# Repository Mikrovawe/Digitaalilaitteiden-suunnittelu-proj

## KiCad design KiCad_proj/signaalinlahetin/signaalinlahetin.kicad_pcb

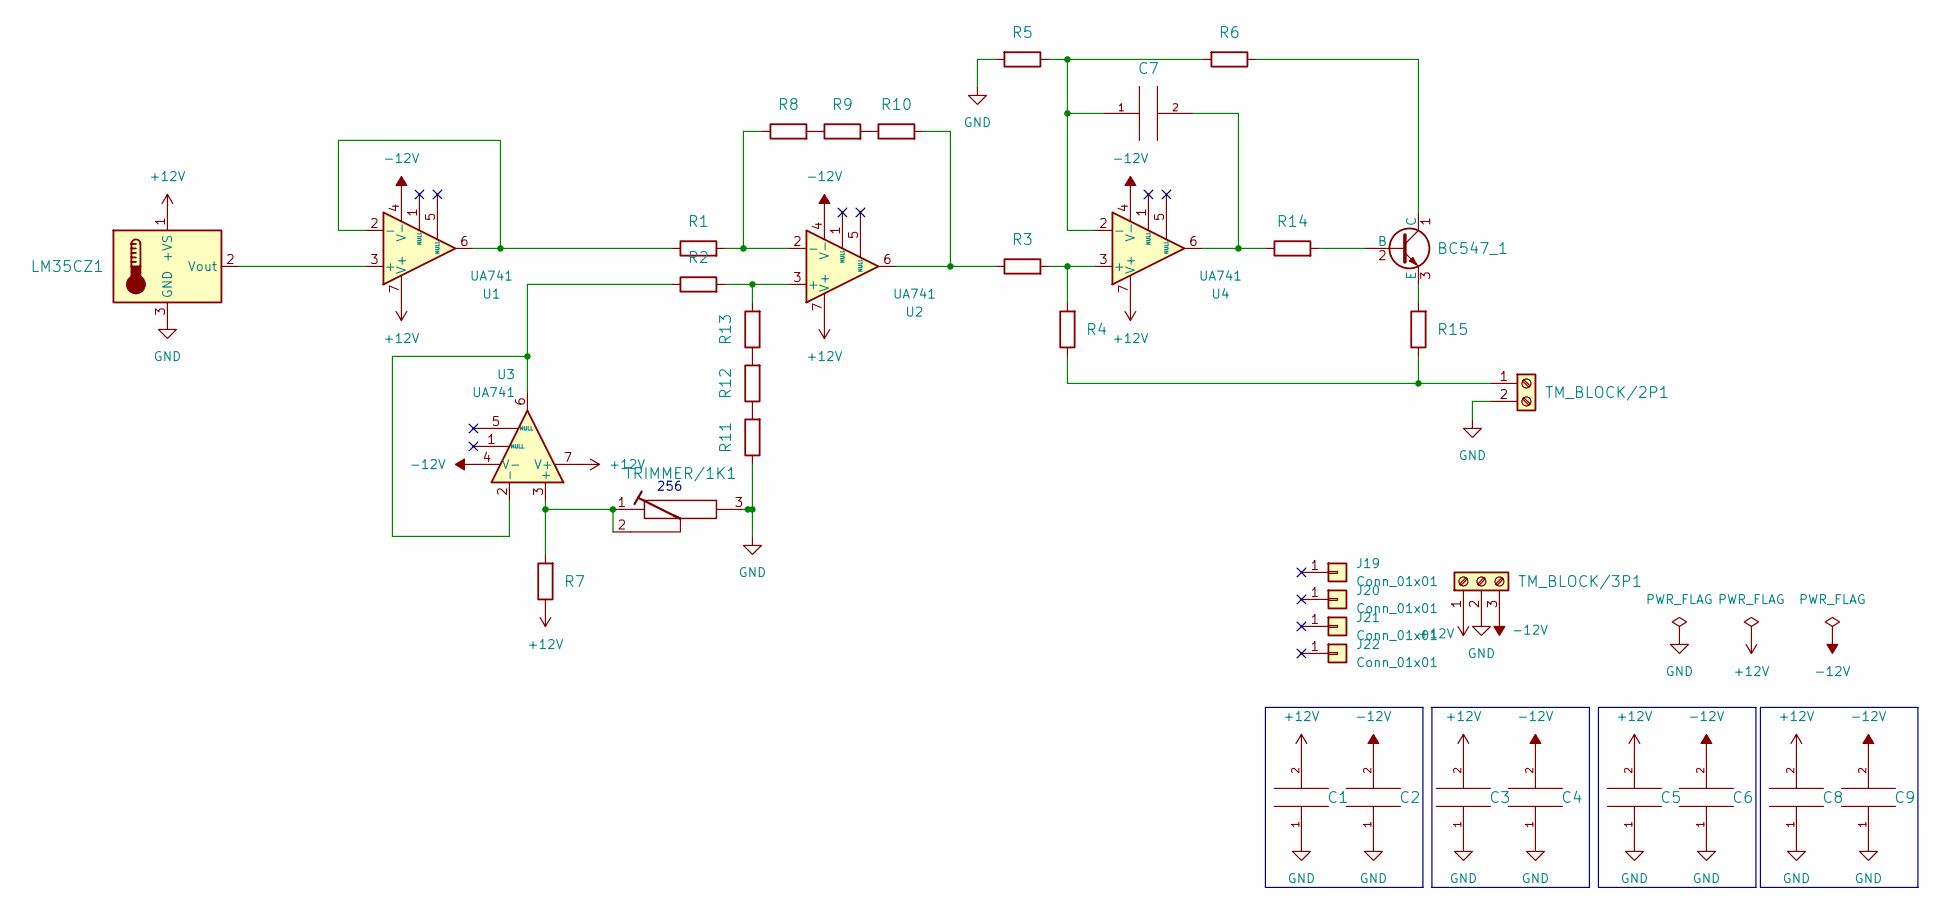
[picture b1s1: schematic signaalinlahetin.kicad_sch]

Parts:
BC547_1: BC547_TO92_0.1A; TO-92
C1, C2, C3, C4, C5, C6, C7, C8, C9: 100NF_50V_CER; C1206; Tolerance +-10%
J19, J20, J21, J22: Conn_01x01; MountingHole_3.5mm_Pad
LM35CZ1: LM35CZ_TO92; TO-92
R1, R2, R7: 10k; 1206; Tolerance +-5%
R3, R4, R5, R6: 150k; 1206; Tolerance +-5%
R8, R11: 1.8k; 1206; Tolerance +-5%
R9, R12: 1.2k; 1206; Tolerance +-5%
R10, R13: 47k; 1206; Tolerance +-5%
R14: 100R; 1206; Tolerance +-5%
R15: 150R; 1206; Tolerance +-5%
TM_BLOCK/2P1: TM_BLOCK_2P
TM_BLOCK/3P1: TM_BLOCK_3P
TRIMMER/1K1: TRIMMER_1K; TRIMMER
U1, U2, U3, U4: UA741; SO8IC

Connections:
+12V: C1.2, C3.2, C5.2, C8.2, LM35CZ1.1 (+VS), R7.1, TM_BLOCK/3P1.1, U1.7 (V+), U2.7 (V+), U3.7 (V+), U4.7 (V+)
-12V: C2.2, C4.2, C6.2, C9.2, TM_BLOCK/3P1.3, U1.4 (V-), U2.4 (V-), U3.4 (V-), U4.4 (V-)
GND: C1.1, C2.1, C3.1, C4.1, C5.1, C6.1, C8.1, C9.1, LM35CZ1.3 (GND), R5.2, R11.1, TM_BLOCK/2P1.2, TM_BLOCK/3P1.2, TRIMMER/1K1.3
unnamed: BC547_1.2 (B), R14.2
unnamed: BC547_1.1 (C), R6.1
unnamed: BC547_1.3 (E), R15.2
unnamed: LM35CZ1.2 (Vout), U1.3 (+)
unnamed: R8.2, R9.1
unnamed: R9.2, R10.1
unnamed: R11.2, R12.1
unnamed: R12.2, R13.1
unnamed: R4.1, R15.1, TM_BLOCK/2P1.1
unnamed: R1.1, U1.2 (-), U1.6
unnamed: R2.2, R13.2, U2.3 (+)
unnamed: R1.2, R8.1, U2.2 (-)
unnamed: R3.1, R10.2, U2.6
unnamed: R7.2, TRIMMER/1K1.1, TRIMMER/1K1.2, U3.3 (+)
unnamed: R2.1, U3.2 (-), U3.6
unnamed: R3.2, R4.2, U4.3 (+)
unnamed: C7.1, R5.1, R6.2, U4.2 (-)
unnamed: C7.2, R14.1, U4.6

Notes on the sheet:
256

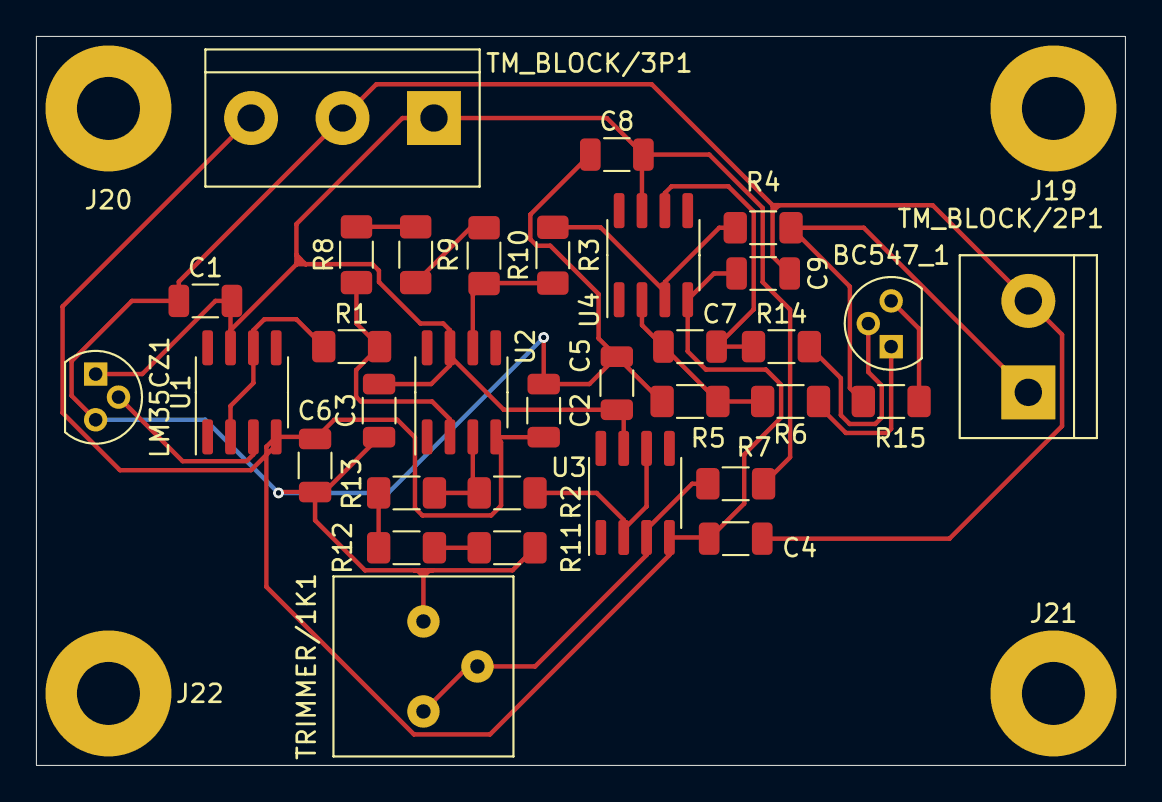
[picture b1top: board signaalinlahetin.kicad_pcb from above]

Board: 2 copper layers, 60.5 x 40.5 mm, 37 parts (0 on the bottom side), 21 nets.
